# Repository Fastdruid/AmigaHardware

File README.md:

# AmigaHardware
Random Amiga Hardware. Some development, some practical

# Licensing

Please check for a license in each individual folder. If there is not one then that design is a fully open design and falls under the MIT license. 
I request that anyone making any derivatives also open source them however I will not restrict the use of them by enforcing it. 

# PiStormInside v1.1 - Tested/Working

Edge slot adaptor to fit an A2000/B2000 Co-Processor card inside the A500 case. Designed to fit PiStorm2k internally but other Co-Processor cards *MAY* fit. 
This does not perform *ANY* Bus Arbitration. If you are not running suitable firmware you will need to remove the existing Processor. 

It is designed to fit entirely between the shield and the casing with the Raspberry Pi soldered to the PiStorm2K. If the Pi is fitted to the header then the shield will need to be removed. 
An appropriate brace is required to support the card (I will design one and upload it here once the prototype arrives).

All pins direct connected with the exception of 9,11,12 & 20.   
9, 11 & 20 contain signals that do not exist on the A500.   
12 is CFGIN which on the A500 is connected directly to ground so to save an extra trace the Co-Processor slot merely connects this also to ground.  

* Rev 3 Requires A2000 version of PiStorm2K as there is no 7MHz on pin 7
* Rev 5 Requires A2000 version of PiStorm2K as there is no 7MHz on pin 7
* Rev6A suggest Bridge JP6 to bring 7MHz to pin 7. Can use PiStorm2K either A2000 or B2000 version.
* Rev8A No mods required. Can use PiStorm2K either A2000 or B2000 version.

Designed as a 4-layer with Ground and (+5V) Power planes however can be made as a 2-layer board with the acceptance that it may not be as stable. 

## Revisions
1.0 - Initial version.
1.1 - Changed thermal relief on the ground plane(s)

# Denise Zorro Co-Processor Riser - Semi Tested

This is a Zorro-II riser to fit an PiStorm2K into a Denise (Mini-ITX Amiga) - https://www.enterlogic.se/?page_id=180 
A Zorro-II slot is 98% the same as the A2000 Co-Processor slot in terms of signals however it is buffered. 
This works in Denise as it utilises non-buffered Zorro-II slots so there is no concern over considering extra delay. 

It may however work on other Zorro-II machines but has only been tested on Denise.

Initially designed to use the "A2000" version of the PiStorm2K which re-generates the 7MHz signal from C1/C3 but this did not work (I suspect due to a dodgy chip on my board). 
Running E7MHz from Pin 92 to Pin 7 and it worked. 
It is however still recommended to use the "A2000" version as this adds a header that can be used for other functionality.

See individual README.md in the folder for more details.

# Zorro DevBoard - UNTESTED

This is a breakout board for Zorro II/III, it does absolutely nothing other than break out all the various contacts to nice pins to allow playing with Zorro cards.

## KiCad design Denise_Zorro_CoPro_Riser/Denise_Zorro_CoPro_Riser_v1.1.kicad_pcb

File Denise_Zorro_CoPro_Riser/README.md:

# Denise Zorro Co-Processor Riser - Semi Tested

This is a Zorro-II riser to fit an PiStorm2K into a Denise (Mini-ITX Amiga) - https://www.enterlogic.se/?page_id=180 
A Zorro-II slot is 98% the same as the A2000 Co-Processor slot in terms of signals however it is buffered. 
This works in Denise as it utilises non-buffered Zorro-II slots so there is no concern over considering extra delay. 

It may however work on other Zorro-II machines but has only been tested on Denise.

Initially designed to use the "A2000" version of the PiStorm2K which re-generates the 7MHz signal from C1/C3 but this did not work (I suspect due to a dodgy chip on my board). 
Running E7MHz from Pin 92 to Pin 7 and it worked. 
It is however still recommended to use the "A2000" version as this adds a header that can be used for other functionality.

### IPL0-2

The A/B2000 utilise IPL0-2 as EINT7, EINT5 & EINT4. These are (justifyably) left off Denise.
To quote Dave Haynie 
>"Only the /INT2 and /INT6 interrupt inputs are actually supported by Commodore-Amiga as part of the Zorro-II specification; the A2000 hardware did not provide the to software the required support mechanisms for the safe use of these lines. 

Unfortunately while justified to leave them off it does mean that things won't work properly. As a result you need either to use link wires under the board to bridge between the processor and the Zorro-II slot or utilise the header included for that purpose on the riser. 

### HDMI

The HDMI out awkwardly *tight* to the Memory if a normal HDMI cable is used. Am angled adaptor is recommended.

### Support

There is no support for the PiStorm2K, it's recommended to firmly attach the Pi to the PiStorm2K and use a spacer on the rear "top" corner to rest against Paula. 

### Bus Arbitration 

This does not do *any* Bus Arbitration. Either special firmware is required or the original 68k needs to be removed. 

### E Clock - Denise Specific

On the A500+ and other later revision Amigas there is a 68R resistor (R109) between the Processor/E (Pin 20) and the Odd/Even CIA chips (Pin 25), E is then connected directly from the CPU to the Edge Slot.
On Denise there is a 68R resistor between the processor and the Zorro-II slot and this is then connected to the Odd/Even CIA chips. 

What this means is how you handle the E-Clock differs if the PiStorm is alone (ie no 68K) or the 68K is still on the board. 

If PiStorm is alone then there is no 68R between it and the Odd/Even CIA and the jumper should be set to "Enable E Clock (+ 68R)".  
If the 68K is still in the socket ***AND*** you have special firmware that disables the E-Clock on the PiStorm then the jumper should be set to "Enable E Clock".

### Special Firmware

I will release the special firmware for PiStorm when it's been further tested! 

#### Swapping between PiStorm and 68k.

Connect Pin 2 of H11 (in between the Zorro slots at the "front") to the header/jumper on PiStorm2K. You can then swap using Num-lock and a reset.

### Version History

v1.0 - Initial design - Built & tested.
V1.1 - Added Zorro-II Pin 92 to Co-Pro Pin 7, adds more text and cleans up a few traces.

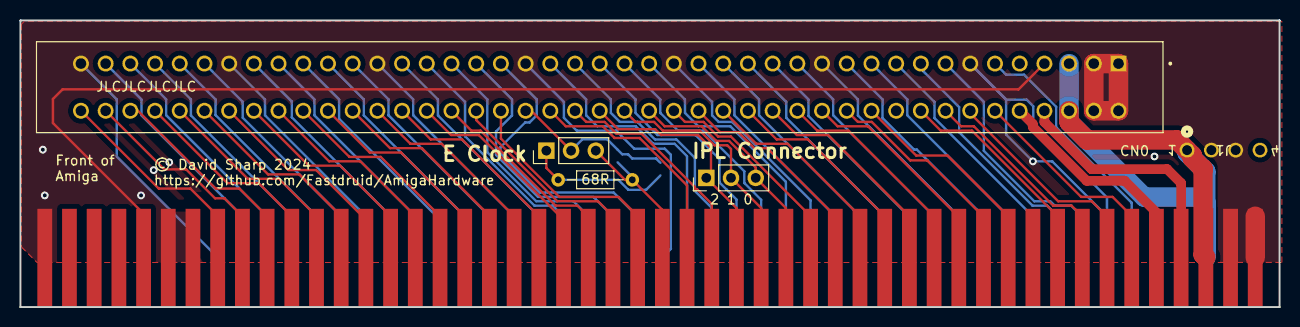
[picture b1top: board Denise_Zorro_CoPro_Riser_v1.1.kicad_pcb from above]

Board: 2 copper layers, 129.5 x 29.5 mm, 4 parts (1 on the bottom side), 73 nets.

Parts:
68R: R_Axial_DIN0204_L3.6mm_D1.6mm_P7.62mm_Horizontal
CN0: Co-Processor; TE_1-5530843-0
CON-Z21: zorro2port; zorro2card
J1: CONN_171826-4_TYCO_TYC

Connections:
+5V: CN0.5, CN0.6, CON-Z21.5, CON-Z21.6, J1.1
+12V: CN0.10, CON-Z21.10, J1.4
-5V: CN0.8, CON-Z21.8
A1: CN0.29, CON-Z21.29
A2: CN0.27, CON-Z21.27
A3: CN0.26, CON-Z21.26
A4: CN0.24, CON-Z21.24
A5: CN0.21, CON-Z21.21
A6: CN0.23, CON-Z21.23
A7: CN0.28, CON-Z21.28
A8: CN0.30, CON-Z21.30
A9: CN0.32, CON-Z21.32
A10: CN0.34, CON-Z21.34
A11: CN0.36, CON-Z21.36
A12: CN0.38, CON-Z21.38
A13: CN0.39, CON-Z21.39
A14: CN0.41, CON-Z21.41
A15: CN0.43, CON-Z21.43
A16: CN0.45, CON-Z21.45
A17: CN0.47, CON-Z21.47
A18: CN0.52, CON-Z21.52
A19: CN0.54, CON-Z21.54
A20: CN0.56, CON-Z21.56
A21: CN0.58, CON-Z21.58
A22: CN0.57, CON-Z21.57
A23: CN0.59, CON-Z21.59
AS: CN0.74, CON-Z21.74
BEER: CN0.46, CON-Z21.46
BG: CN0.64, CON-Z21.64
BGACK: CN0.62, CON-Z21.62
BR: CN0.60, CON-Z21.60
CCK: CN0.16, CON-Z21.16
CCKQ: CN0.14, CON-Z21.14
CDAC: CN0.15, CON-Z21.15
CFGIN: CN0.12, CON-Z21.12
CFGOUT: CN0.11, CON-Z21.11
D0: CN0.75, CON-Z21.75
D1: CN0.77, CON-Z21.77
D2: CN0.79, CON-Z21.79
D3: CN0.81, CON-Z21.81
D4: CN0.83, CON-Z21.83
D5: CN0.86, CON-Z21.86
D6: CN0.84, CON-Z21.84
D7: CN0.82, CON-Z21.82
D8: CN0.80, CON-Z21.80
D9: CN0.78, CON-Z21.78
D10: CN0.76, CON-Z21.76
D11: CN0.71, CON-Z21.71
D12: CN0.69, CON-Z21.69
D13: CN0.67, CON-Z21.67
D14: CN0.65, CON-Z21.65
D15: CN0.63, CON-Z21.63
DTACK: CN0.66, CON-Z21.66
E7MHz: CN0.7, CON-Z21.92
ECLock: 68R.1, CON-Z21.50
FC0: CN0.31, CON-Z21.31
FC1: CN0.33, CON-Z21.33
FC2: CN0.35, CON-Z21.35
GND: CN0.1, CN0.2, CN0.3, CN0.4, CN0.13, CN0.25, CN0.37, CN0.49, CN0.61, CN0.73, CN0.85, CON-Z21.1, CON-Z21.2, CON-Z21.3, CON-Z21.4, CON-Z21.13, CON-Z21.25, CON-Z21.37, CON-Z21.49, CON-Z21.61, CON-Z21.73, CON-Z21.85, CON-Z21.87, CON-Z21.88, CON-Z21.89, CON-Z21.90, CON-Z21.91, CON-Z21.99, CON-Z21.100, J1.2, J1.3
HLT: CN0.55, CON-Z21.55
INT2: CN0.19, CON-Z21.19
INT6: CN0.22, CON-Z21.22
IPL0: CN0.40, CON-Z21.40
IPL1: CN0.42, CON-Z21.42
IPL2: CN0.44, CON-Z21.44
LDS: CN0.70, CON-Z21.70
OVR: CN0.17, CON-Z21.17
RST: CN0.53, CON-Z21.53
R_W: CN0.68, CON-Z21.68
UDS: CN0.72, CON-Z21.72
VMA: CN0.51, CON-Z21.51
VPA: CN0.48, CON-Z21.48
XRDY: CN0.18, CON-Z21.18

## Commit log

2024-02-20 Added PiStormInside
2024-02-20 Added KiCad file
2024-02-22 Added Denise Zorro Co-Processor Riser
2024-03-04 Updated from v1.0 to v1.1
    Changed thermal reliefs as it was a bitch to solder them with (effectively) 3 ground planes.
2024-03-04 Delete PiStormInside/PiStormInside_Final.zip
    Removed v1.0 gerbers
2024-03-04 Create LICENSE

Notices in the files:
Denise_Zorro_CoPro_Riser/Denise_Zorro_CoPro_Riser_v1.1.kicad_pcb:
© David Sharp 2024
